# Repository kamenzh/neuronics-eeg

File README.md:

# Neuronic

An open development project for an affordable eight-channel EEG acquisition
PCB, ESP32 wireless streaming and PC-based signal processing and classification.

**Current revision A0.5** increases electrode series resistance, revises input filtering and rail discharge, updates the battery PTC and keys the controller harness. See the [protection review](docs/A0_5_PROTECTION.md) and [checked fabrication and hand-assembly files](hardware/fabrication/A0.5/). The Sino-k connector inquiry and assembled-system qualification are open.
There is no manufactured or body-validated Neuronic board yet. This repository
contains genuine KiCad source, not a manufacturing release.

**The target is a working eight-channel EEG instrument.** Bench testing is a
development phase; actual acquisition and person-use readiness still need
implementation, measurements and qualified system review. See the
[working-system acceptance plan](docs/SYSTEM_ACCEPTANCE_PLAN.md).

**November 19 follow-up:** the [independent November 17 report](docs/reviews/independent-577aad8-2026-11-17/REPORT.md)
is incorporated, the BOM prose is corrected, and a
[connector drawing/CAD audit](docs/CONNECTOR_VERIFICATION_A0_3.md) records what is
known and what still needs physical evidence. A0.5 fabrication data are available for review. Manufacturer selection and ordering are pending.

**A0.3 implements the main A0.2 review fixes:** revised analog routing,
stronger default logic pulls, two power-off tolerant interface buffers, extra
reference capacitance and revised socket mounting slots. Read the
[changes and remaining gates](docs/REVIEW_FIXES_A0_3.md). Historical
[A0.2 findings](docs/INDEPENDENT_REVIEW_A0_2.md) remain available.

**A0.5 controller cable.** Pin 1 is ground, position 2 is the mechanical key and must have no wire, pin 11 takes Nano 3V3, and pin 12 is GPIO6 enable. See the [cable pinout](docs/POWER_HARNESS_A0_3.md) and [keying instructions](docs/A0_5_PROTECTION.md).

**Controller selected: use the Waveshare ESP32-S3-Nano you already own.**
The Sino-k SGE117DN ten-lead set is recorded; P1 36619 touchproof sockets are selected; physical plug fit still needs verification. See [the wiring and power plan](docs/CONTROLLER_AND_ELECTRODES.md)
and [the step-by-step roadmap](docs/NEXT_STEPS.md).

**First time using KiCad? Read [START_HERE](docs/START_HERE.md).** Open
[`hardware/kicad/neuronic.kicad_pro`](hardware/kicad/neuronic.kicad_pro) in KiCad.

## System

```mermaid
flowchart TD
    E["8 contacts + reference"] --> P["Input networks"]
    P --> A["ADS1299: PGAs and simultaneous ADCs"]
    A -->|"3.3 V SPI"| M["External ESP32"]
    A --> B["Limited bias output: tenth contact"]
    M -->|"Wireless"| C["PC: recording and classification"]
    V["Battery and regulators"] --> A
```

| Parameter | A0.5 design target |
| --- | --- |
| Recording channels | 8 simultaneous |
| Contacts | 8 recording + 1 reference + 1 bias |
| Front end | ADS1299IPAG, programmable gain, 24-bit output |
| Initial rate | 250 samples/s/channel |
| Analog / ADC digital supplies | 5 V / 3.3 V |
| Input power | 6 x AA alkaline candidate; no charger |
| Controller interface | Waveshare ESP32-S3-Nano via 12-pin 3.3 V SPI header |
| PCB | 88 x 90 mm, four copper layers, routed bench prototype |

The ADS1299 already supplies the amplification and conversion. An additional
high-gain analog amplifier chain is not assumed. Nominal ADC bit depth is not
a claim of noise-free resolution, and more gain can reduce offset headroom.

## Repository map

| Path | Contents |
| --- | --- |
| `hardware/kicad/` | Main project, four schematic sheets, PCB, custom symbols and bundled footprints |
| `hardware/bom/` | Per-component and grouped candidate MPN lists; not an order release |
| `hardware/parts.json` | Editable candidate component catalog |
| `hardware/interface.json` | Selected controller GPIO, electrode and power contract |
| `hardware/design.json` | Generated component/net/placement record |
| `hardware/validation/` | Exported netlist, connectivity audit, DRC, RC calculation and sheet previews |
| `hardware/fabrication/` | A0.5 Gerber/drill package and assembly references for review |
| `firmware/` | Acquisition firmware specification; implementation pending |
| `software/` | PC receiver/recorder specification; implementation pending |
| `ml/` | Evaluation plan; no trained classifier yet |
| `experiments/` | Recording and validation protocols |
| `docs/` | Beginner guide, design decisions, open blockers and bench plan |
| `tools/` | Reproducible hardware generator and validation commands |
| `data/` | Local private recordings; contents ignored by Git |

The old CortexLink README is retained in `docs/archive/initial-README.md`.
The empty duplicate KiCad scaffolds were removed; their originals remain in
the repository history at `ae7d76e`.

## Verification

Read [the current status](hardware/validation/STATUS.md) before using the files.
Checks compare the **actual KiCad-exported netlist** with the source, component
footprints and an independent physical pin contract. They do not prove analog
performance, layout quality or body safety.

```bash
/usr/bin/python3 tools/validate_kicad.py
python3 tools/prepare_bom.py
python3 tools/review_electrical.py
python3 tools/check_contact_faults.py
python3 tools/simulate_input.py
/usr/bin/python3 -m unittest discover -s tests -v
```

Validation uses KiCad 9; on Linux use its compatible `/usr/bin/python3` for pcbnew. Read the current validation report for routing and CAD results; manufacturing and body-use approval remain separate. GUI ERC/DRC instructions are in the beginner guide.

See the [current protection review](docs/A0_5_PROTECTION.md) and [power and cable guide](docs/POWER_HARNESS_A0_3.md) for the circuit decisions and physical checks.

## Roadmap

- [x] Consolidate project and document circuit decisions.
- [x] Create editable KiCad sheets, footprint bundle, BOM and placed PCB.
- [x] Export and audit connectivity; perform limited ideal RC calculation.
- [ ] Close input-protection, connector, bias-loop and power-review blockers.
- [x] Complete a routed bench checkpoint with clean ERC and schematic-parity DRC.
- [x] Complete a separate AI review of the saved circuit and layout, with fresh checks and written findings.
- [x] Implement the main circuit/layout fixes and update checks/harness documentation.
- [ ] Verify physical fit and complete manufacturing-release review.
- [x] Select exact candidate PCB MPNs and the owned controller.
- [ ] Verify procurement details and compare delivered bare-board quotes.
- [ ] Fabricate a small prototype batch and complete bench tests.
- [ ] Implement and verify acquisition, raw recording and loss accounting.
- [ ] Review final body-connected design before scalp testing.
- [ ] Record repeatable EEG, then evaluate baselines and a CNN across sessions.

## Experiments and safety

The immediate target is trustworthy acquisition and a repeatable alpha
experiment. Intentional command classification follows measured signal quality.
EEG does not directly reveal arbitrary thoughts. Eye and muscle artifacts must
be checked, and train/test data must be separated by complete trials/sessions.

This is a body-connected engineering project, not a diagnostic device. A0.5 still needs
bench qualification and complete-system electrical safety review. Do not attach it to a person. Final electrode
protection and fault paths need qualified review before any scalp recording.
Battery power, ERC and DRC alone do not establish safety. During approved
recording, use a self-contained battery arrangement and wireless communication,
with USB, chargers and mains-connected instruments disconnected.

## Sources and licensing

See [design decisions and primary sources](docs/DESIGN_DECISIONS.md),
[open blockers](docs/REVIEW_BLOCKERS.md) and [third-party notices](hardware/licenses/).
The repository's existing MIT license is preserved for original work. Bundled
KiCad library assets retain their own license and design-use exception. No
third-party EEG hardware project has been silently relicensed or included.

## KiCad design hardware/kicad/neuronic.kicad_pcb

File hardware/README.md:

# Hardware

Open `kicad/neuronic.kicad_pro`. Read `validation/STATUS.md` and
`../docs/START_HERE.md` first.

`design.json` is generated by `tools/generate_hardware.py` and describes the
component/net/placement checkpoint. It is not a substitute for the actual
KiCad schematic or DRC. `bom/bom-review.csv` lists candidate parts and unresolved
MPNs; it is not a purchase-ready BOM.

KiCad source, script and review docs belong in Git. Fabrication files should
only be exported for reviewed, tagged hardware revisions.

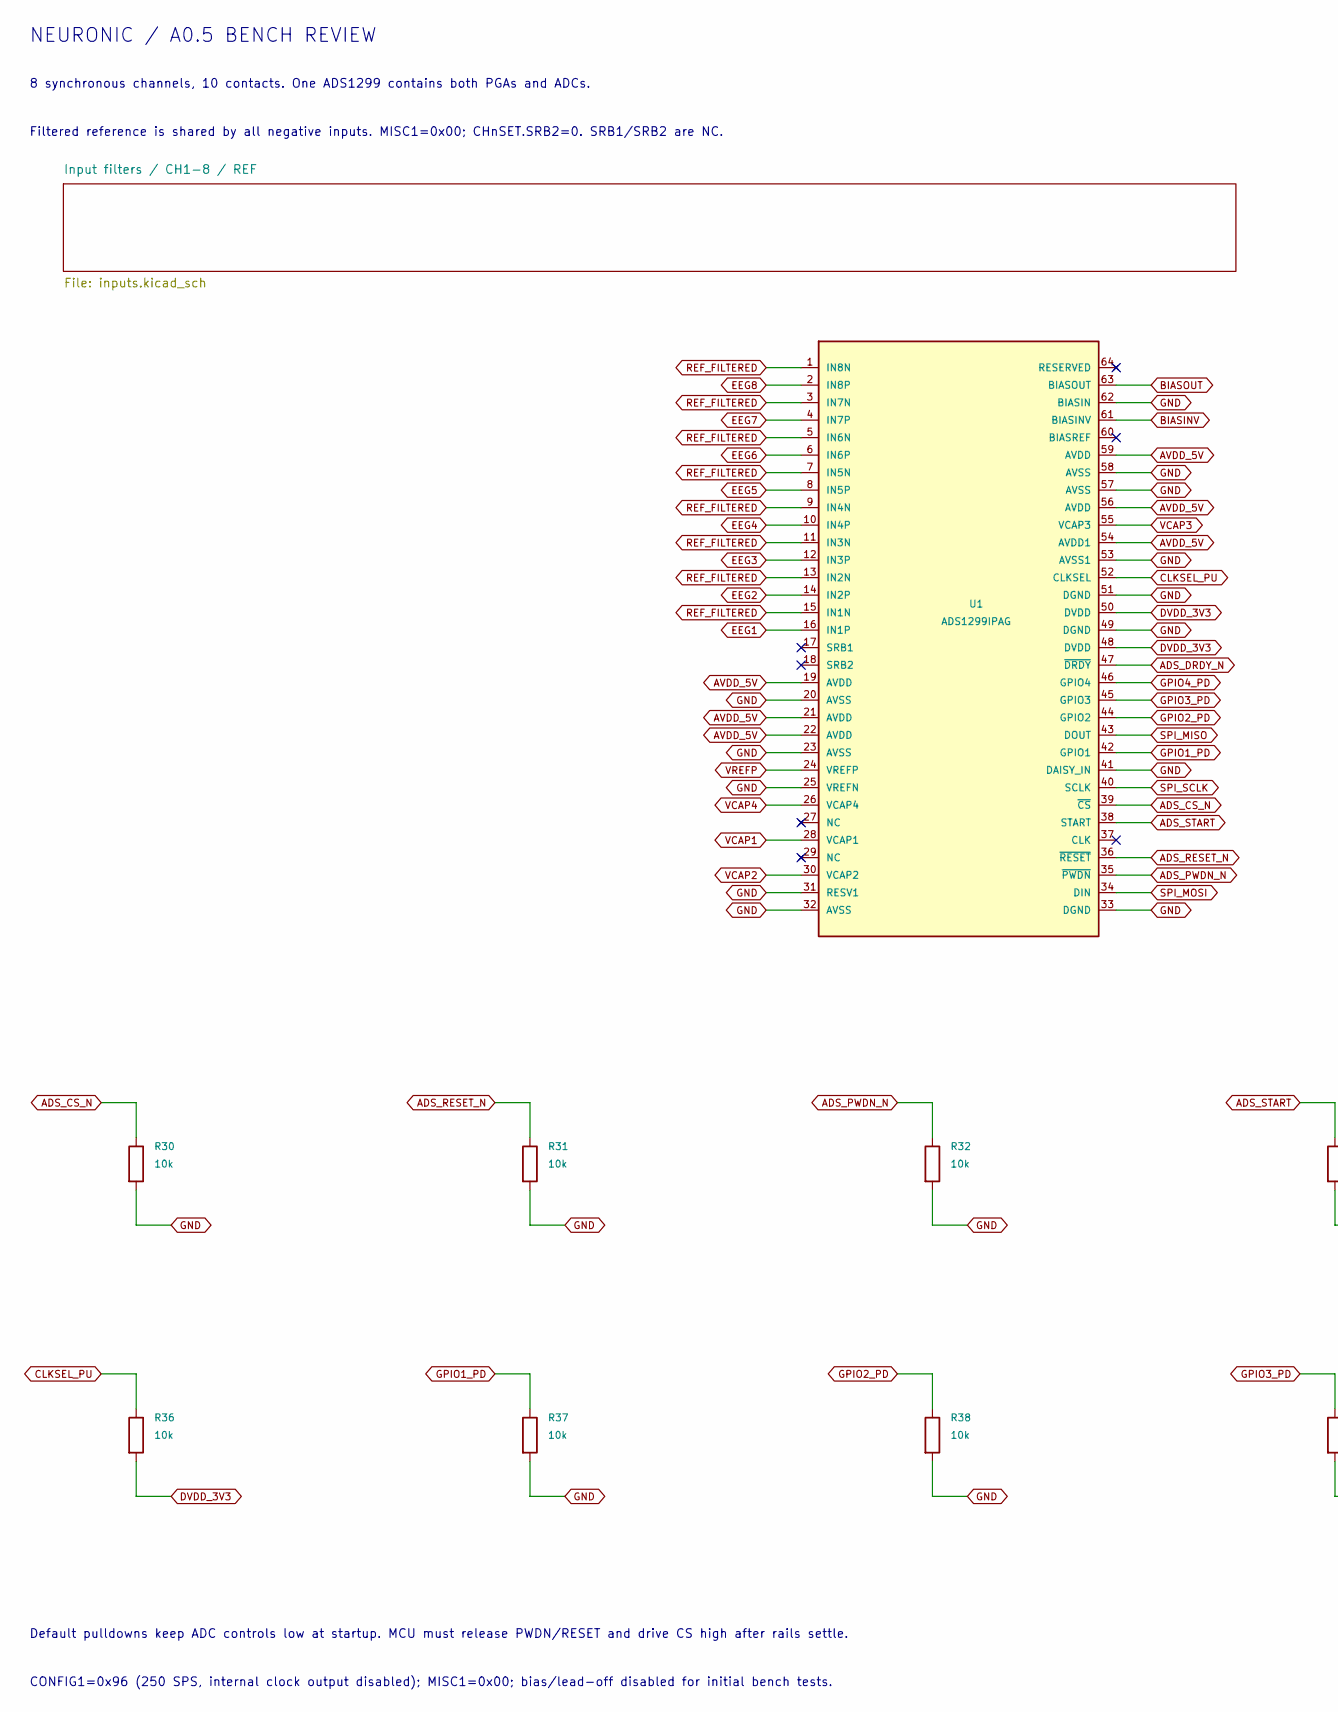
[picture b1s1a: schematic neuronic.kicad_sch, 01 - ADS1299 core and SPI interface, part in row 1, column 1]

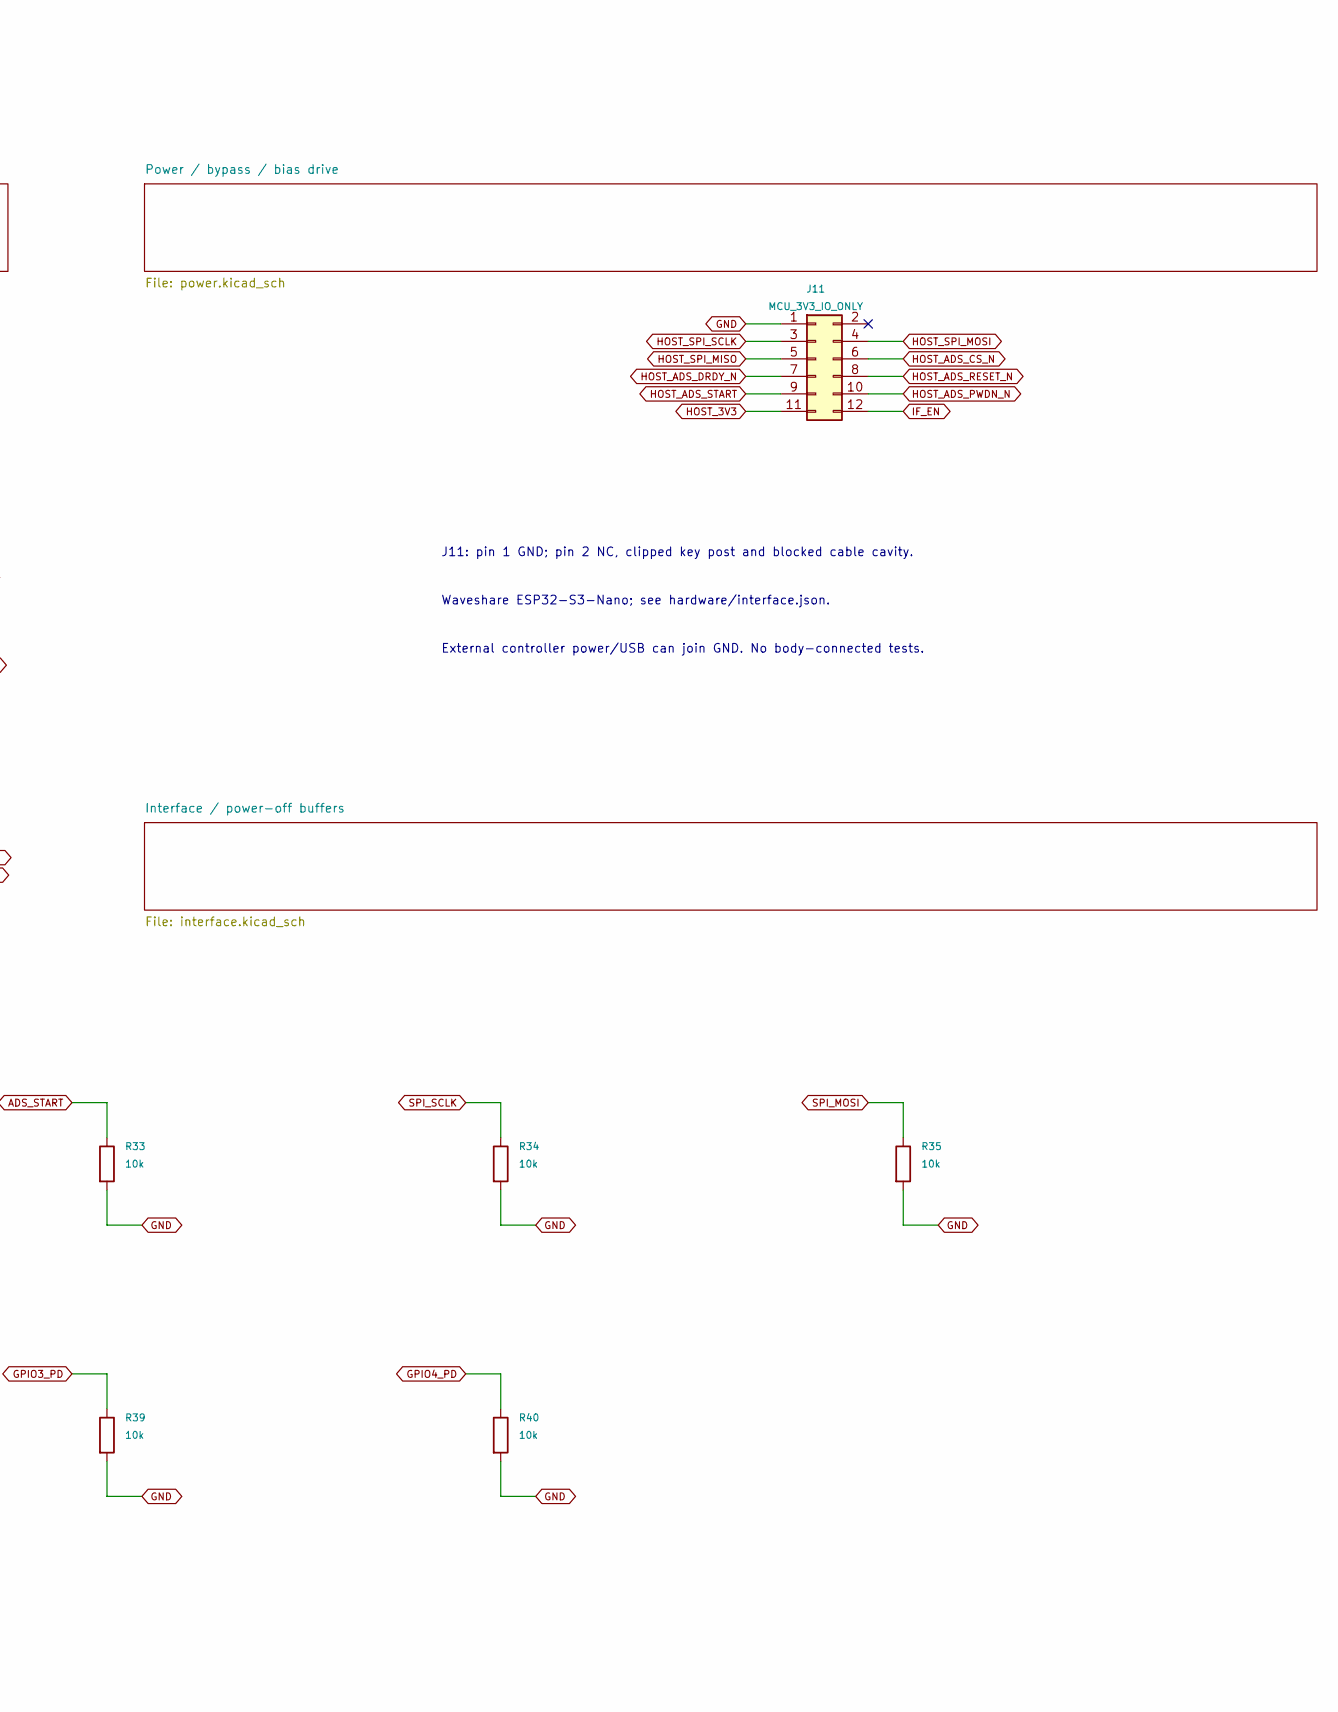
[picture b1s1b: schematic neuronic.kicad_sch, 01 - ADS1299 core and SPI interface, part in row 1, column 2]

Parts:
J11: MCU_3V3_IO_ONLY; PinHeader_2x06_P2.54mm_Vertical
R30, R31, R32, R33, R34, R35, R36, R37, R38, R39, R40: 10k; R_0805_2012Metric
U1: ADS1299IPAG; TQFP-64_10x10mm_P0.5mm

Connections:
ADS_CS_N: R30.1, U1.39 (~CS); also elsewhere on the board
ADS_DRDY_N: U1.47 (~DRDY); also elsewhere on the board
ADS_PWDN_N: R32.1, U1.35 (~PWDN); also elsewhere on the board
ADS_RESET_N: R31.1, U1.36 (~RESET); also elsewhere on the board
ADS_START: R33.1, U1.38 (START); also elsewhere on the board
AVDD_5V: U1.19 (AVDD), U1.21 (AVDD), U1.22 (AVDD), U1.54 (AVDD1), U1.56 (AVDD), U1.59 (AVDD); also elsewhere on the board
BIASINV: U1.61 (BIASINV); also elsewhere on the board
BIASOUT: U1.63 (BIASOUT); also elsewhere on the board
CLKSEL_PU: R36.1, U1.52 (CLKSEL)
DVDD_3V3: R36.2, U1.48 (DVDD), U1.50 (DVDD); also elsewhere on the board
EEG1: U1.16 (IN1P); also elsewhere on the board
EEG2: U1.14 (IN2P); also elsewhere on the board
EEG3: U1.12 (IN3P); also elsewhere on the board
EEG4: U1.10 (IN4P); also elsewhere on the board
EEG5: U1.8 (IN5P); also elsewhere on the board
EEG6: U1.6 (IN6P); also elsewhere on the board
EEG7: U1.4 (IN7P); also elsewhere on the board
EEG8: U1.2 (IN8P); also elsewhere on the board
GND: J11.1, R30.2, R31.2, R32.2, R33.2, R34.2, R35.2, R37.2, R38.2, R39.2, R40.2, U1.20 (AVSS), U1.23 (AVSS), U1.25 (VREFN), U1.31 (RESV1), U1.32 (AVSS), U1.33 (DGND), U1.41 (DAISY_IN), U1.49 (DGND), U1.51 (DGND), U1.53 (AVSS1), U1.57 (AVSS), U1.58 (AVSS), U1.62 (BIASIN); also elsewhere on the board
GPIO1_PD: R37.1, U1.42 (GPIO1)
GPIO2_PD: R38.1, U1.44 (GPIO2)
GPIO3_PD: R39.1, U1.45 (GPIO3)
GPIO4_PD: R40.1, U1.46 (GPIO4)
HOST_3V3: J11.11; also elsewhere on the board
HOST_ADS_CS_N: J11.6; also elsewhere on the board
HOST_ADS_DRDY_N: J11.7; also elsewhere on the board
HOST_ADS_PWDN_N: J11.10; also elsewhere on the board
HOST_ADS_RESET_N: J11.8; also elsewhere on the board
HOST_ADS_START: J11.9; also elsewhere on the board
HOST_SPI_MISO: J11.5; also elsewhere on the board
HOST_SPI_MOSI: J11.4; also elsewhere on the board
HOST_SPI_SCLK: J11.3; also elsewhere on the board
IF_EN: J11.12; also elsewhere on the board
REF_FILTERED: U1.1 (IN8N), U1.3 (IN7N), U1.5 (IN6N), U1.7 (IN5N), U1.9 (IN4N), U1.11 (IN3N), U1.13 (IN2N), U1.15 (IN1N); also elsewhere on the board
SPI_MISO: U1.43 (DOUT); also elsewhere on the board
SPI_MOSI: R35.1, U1.34 (DIN); also elsewhere on the board
SPI_SCLK: R34.1, U1.40 (SCLK); also elsewhere on the board
VCAP1: U1.28 (VCAP1); also elsewhere on the board
VCAP2: U1.30 (VCAP2); also elsewhere on the board
VCAP3: U1.55 (VCAP3); also elsewhere on the board
VCAP4: U1.26 (VCAP4); also elsewhere on the board
VREFP: U1.24 (VREFP); also elsewhere on the board

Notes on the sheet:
NEURONIC / A0.5 BENCH REVIEW
8 synchronous channels, 10 contacts. One ADS1299 contains both PGAs and ADCs.
Filtered reference is shared by all negative inputs. MISC1=0x00; CHnSET.SRB2=0. SRB1/SRB2 are NC.
J11: pin 1 GND; pin 2 NC, clipped key post and blocked cable cavity.
Waveshare ESP32-S3-Nano; see hardware/interface.json.
External controller power/USB can join GND. No body-connected tests.
Default pulldowns keep ADC controls low at startup. MCU must release PWDN/RESET and drive CS high after rails settle.
CONFIG1=0x96 (250 SPS, internal clock output disabled); MISC1=0x00; bias/lead-off disabled for initial bench tests.

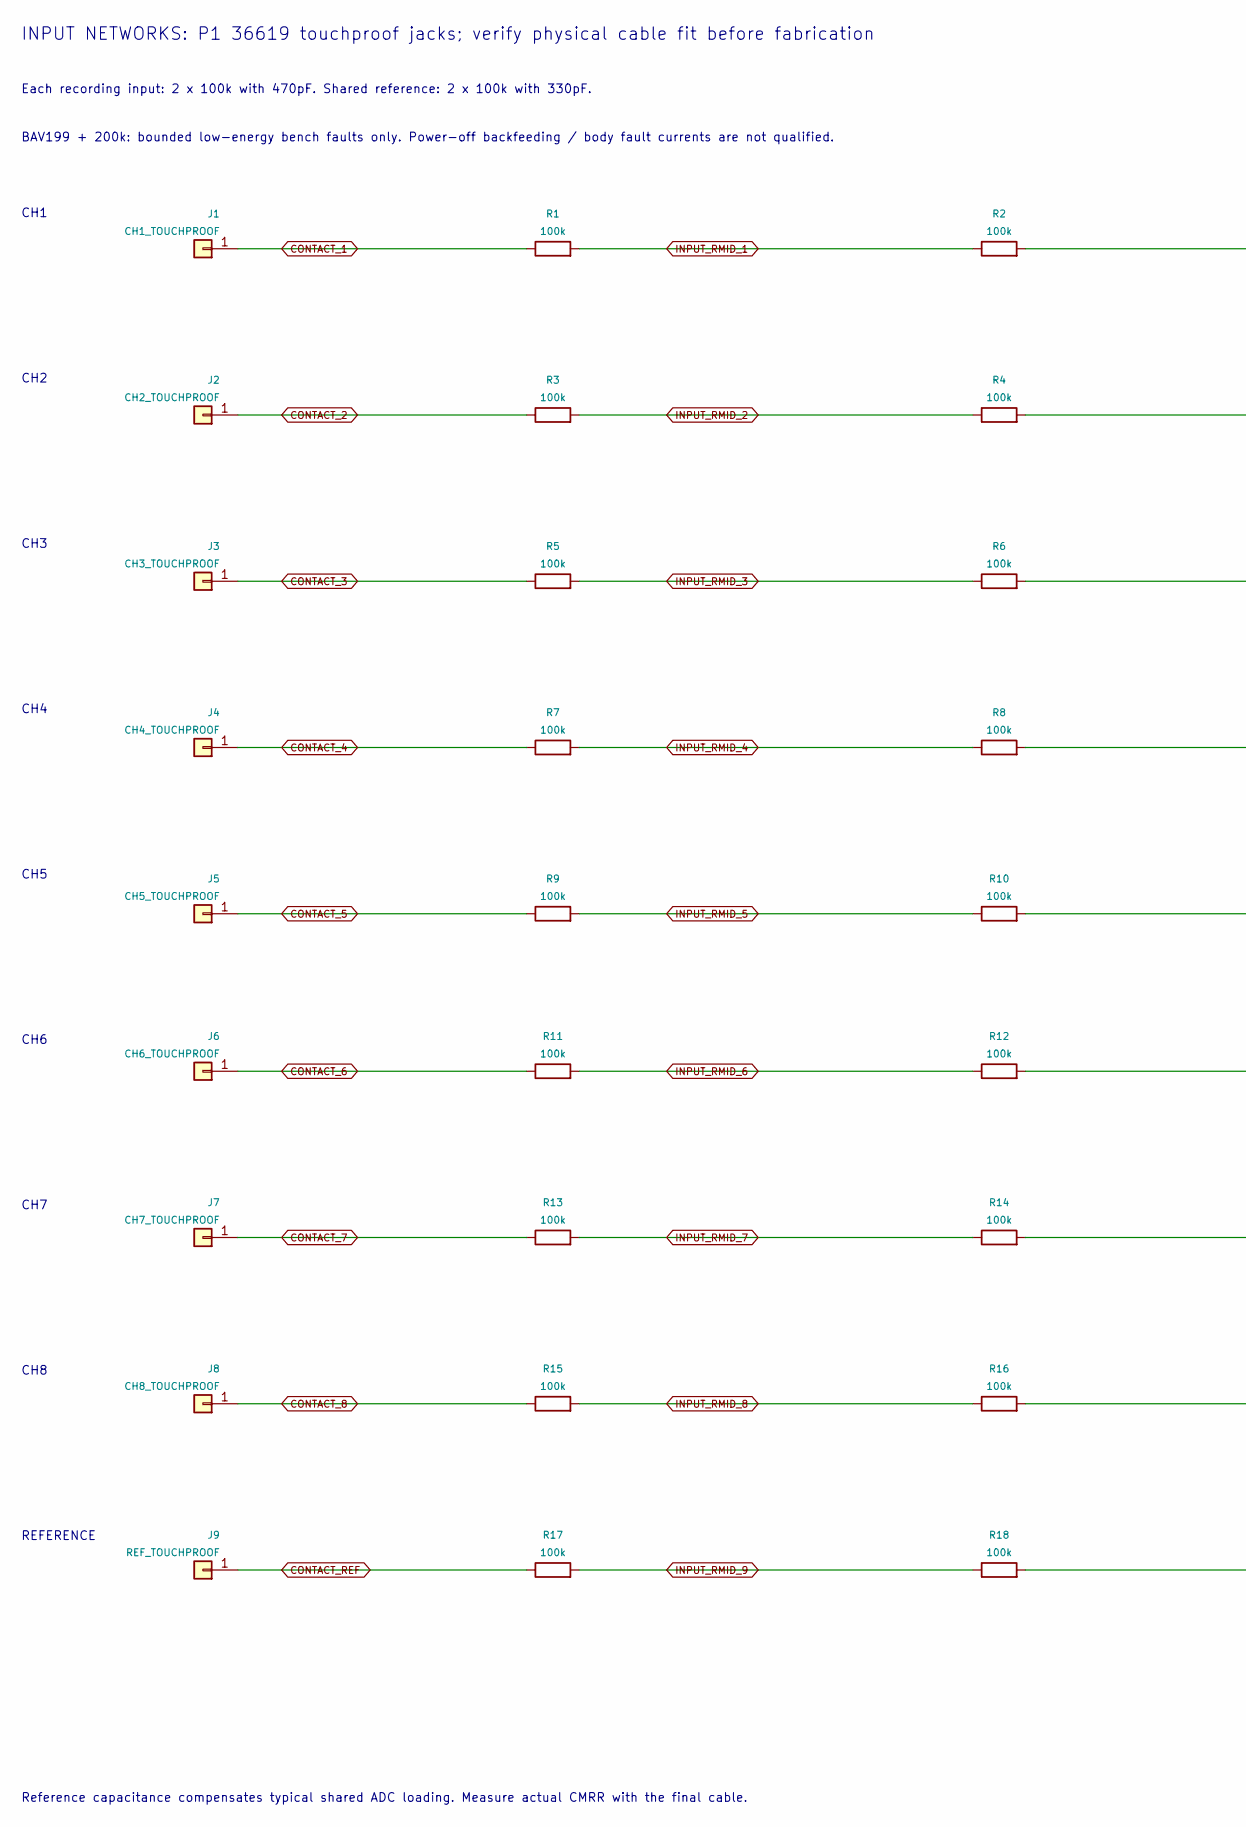
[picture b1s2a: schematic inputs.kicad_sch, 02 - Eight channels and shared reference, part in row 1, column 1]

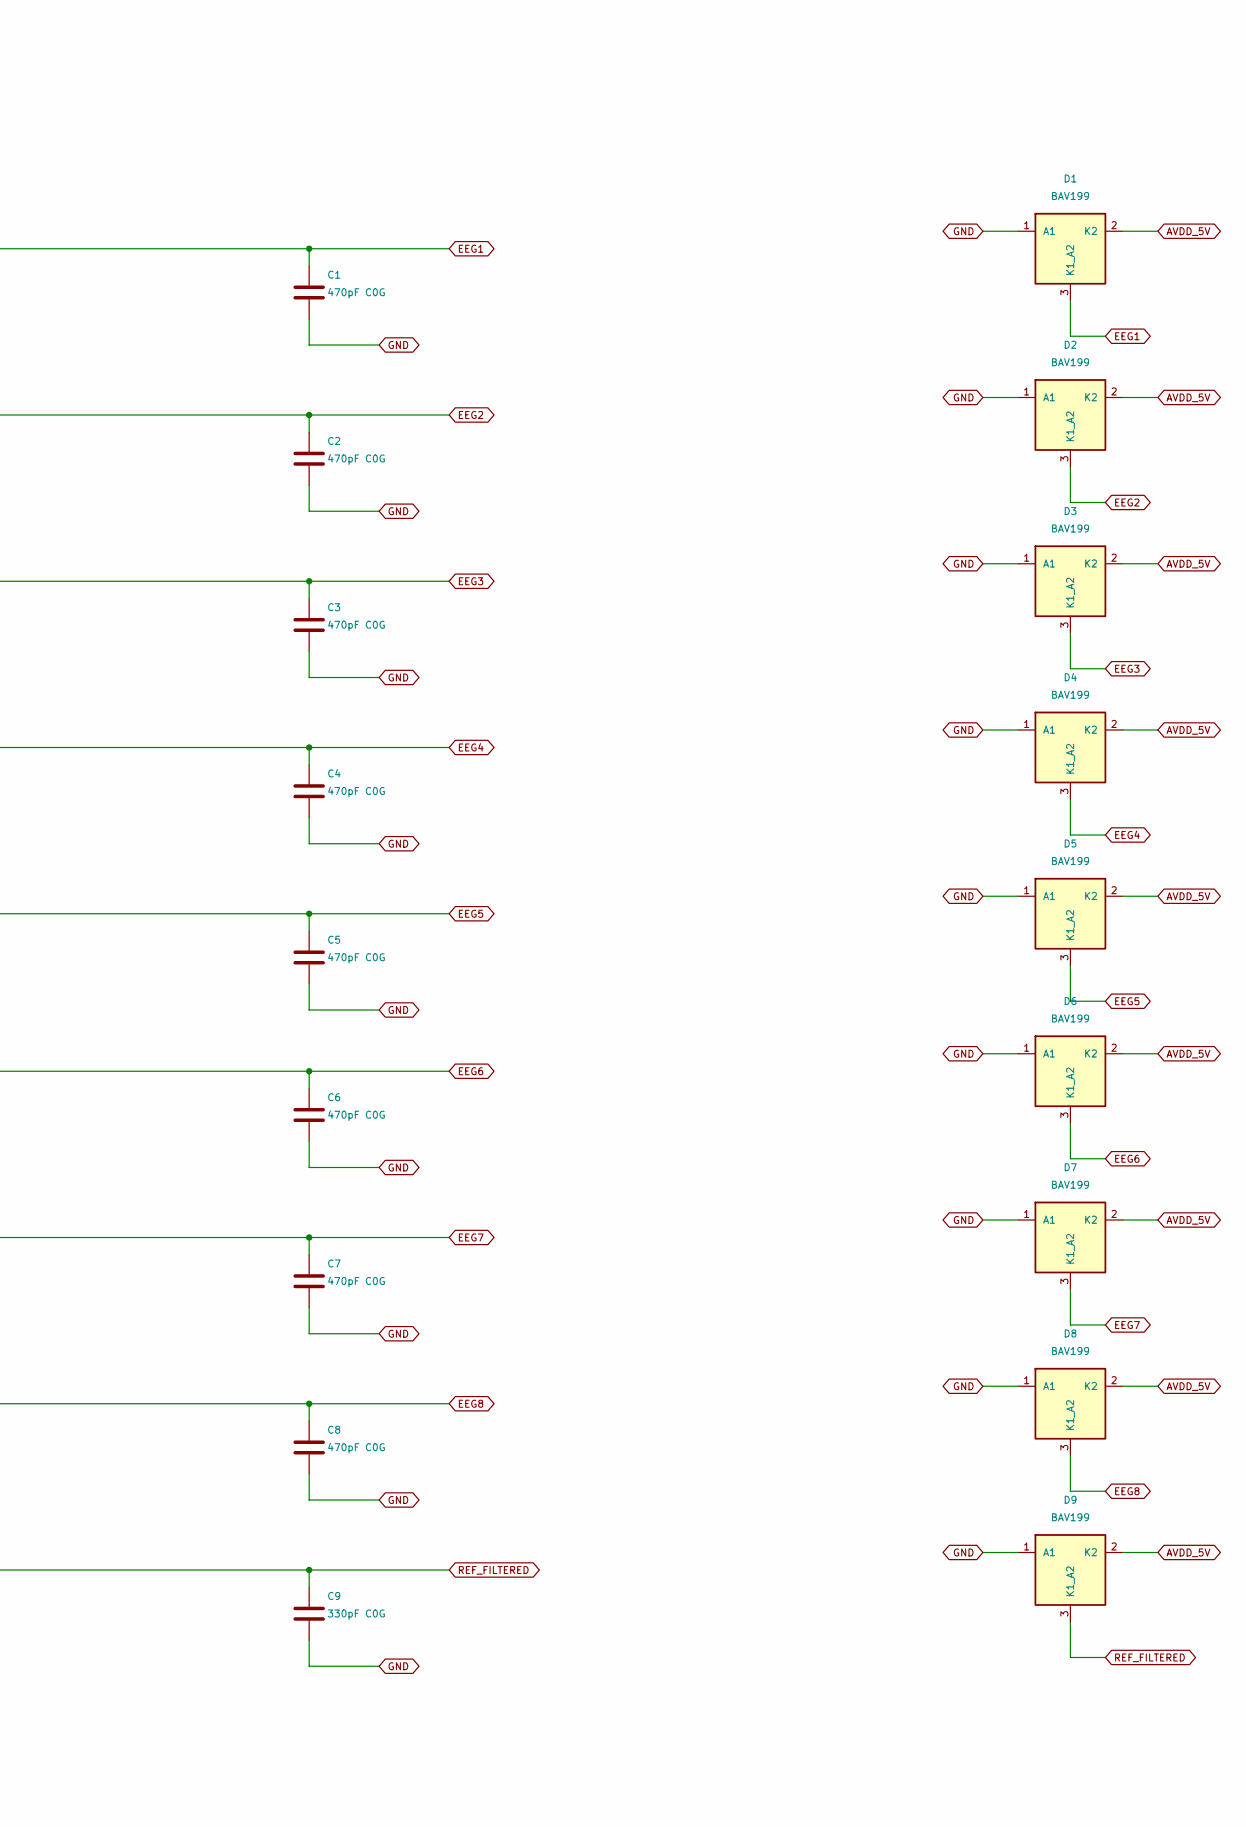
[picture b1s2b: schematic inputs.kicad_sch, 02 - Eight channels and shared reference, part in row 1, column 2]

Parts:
C1, C2, C3, C4, C5, C6, C7, C8: 470pF C0G; C_0805_2012Metric
C9: 330pF C0G; C_0805_2012Metric
D1, D2, D3, D4, D5, D6, D7, D8, D9: BAV199; SOT-23
J1: CH1_TOUCHPROOF; P1_36619_Touchproof_RA
J2: CH2_TOUCHPROOF; P1_36619_Touchproof_RA
J3: CH3_TOUCHPROOF; P1_36619_Touchproof_RA
J4: CH4_TOUCHPROOF; P1_36619_Touchproof_RA
J5: CH5_TOUCHPROOF; P1_36619_Touchproof_RA
J6: CH6_TOUCHPROOF; P1_36619_Touchproof_RA
J7: CH7_TOUCHPROOF; P1_36619_Touchproof_RA
J8: CH8_TOUCHPROOF; P1_36619_Touchproof_RA
J9: REF_TOUCHPROOF; P1_36619_Touchproof_RA
R1, R2, R3, R4, R5, R6, R7, R8, R9, R10, R11, R12, R13, R14, R15, R16, R17, R18: 100k; R_0805_2012Metric

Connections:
AVDD_5V: D1.2 (K2), D2.2 (K2), D3.2 (K2), D4.2 (K2), D5.2 (K2), D6.2 (K2), D7.2 (K2), D8.2 (K2), D9.2 (K2); also elsewhere on the board
CONTACT_1: J1.1, R1.1
CONTACT_2: J2.1, R3.1
CONTACT_3: J3.1, R5.1
CONTACT_4: J4.1, R7.1
CONTACT_5: J5.1, R9.1
CONTACT_6: J6.1, R11.1
CONTACT_7: J7.1, R13.1
CONTACT_8: J8.1, R15.1
CONTACT_REF: J9.1, R17.1
EEG1: C1.1, D1.3 (K1_A2), R2.2; also elsewhere on the board
EEG2: C2.1, D2.3 (K1_A2), R4.2; also elsewhere on the board
EEG3: C3.1, D3.3 (K1_A2), R6.2; also elsewhere on the board
EEG4: C4.1, D4.3 (K1_A2), R8.2; also elsewhere on the board
EEG5: C5.1, D5.3 (K1_A2), R10.2; also elsewhere on the board
EEG6: C6.1, D6.3 (K1_A2), R12.2; also elsewhere on the board
EEG7: C7.1, D7.3 (K1_A2), R14.2; also elsewhere on the board
EEG8: C8.1, D8.3 (K1_A2), R16.2; also elsewhere on the board
GND: C1.2, C2.2, C3.2, C4.2, C5.2, C6.2, C7.2, C8.2, C9.2, D1.1 (A1), D2.1 (A1), D3.1 (A1), D4.1 (A1), D5.1 (A1), D6.1 (A1), D7.1 (A1), D8.1 (A1), D9.1 (A1); also elsewhere on the board
INPUT_RMID_1: R1.2, R2.1
INPUT_RMID_2: R3.2, R4.1
INPUT_RMID_3: R5.2, R6.1
INPUT_RMID_4: R7.2, R8.1
INPUT_RMID_5: R9.2, R10.1
INPUT_RMID_6: R11.2, R12.1
INPUT_RMID_7: R13.2, R14.1
INPUT_RMID_8: R15.2, R16.1
INPUT_RMID_9: R17.2, R18.1
REF_FILTERED: C9.1, D9.3 (K1_A2), R18.2; also elsewhere on the board

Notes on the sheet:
INPUT NETWORKS: P1 36619 touchproof jacks; verify physical cable fit before fabrication
Each recording input: 2 x 100k with 470pF. Shared reference: 2 x 100k with 330pF.
BAV199 + 200k: bounded low-energy bench faults only. Power-off backfeeding / body fault currents are not qualified.
CH1
CH2
CH3
CH4
CH5
CH6
CH7
CH8
REFERENCE
Reference capacitance compensates typical shared ADC loading. Measure actual CMRR with the final cable.

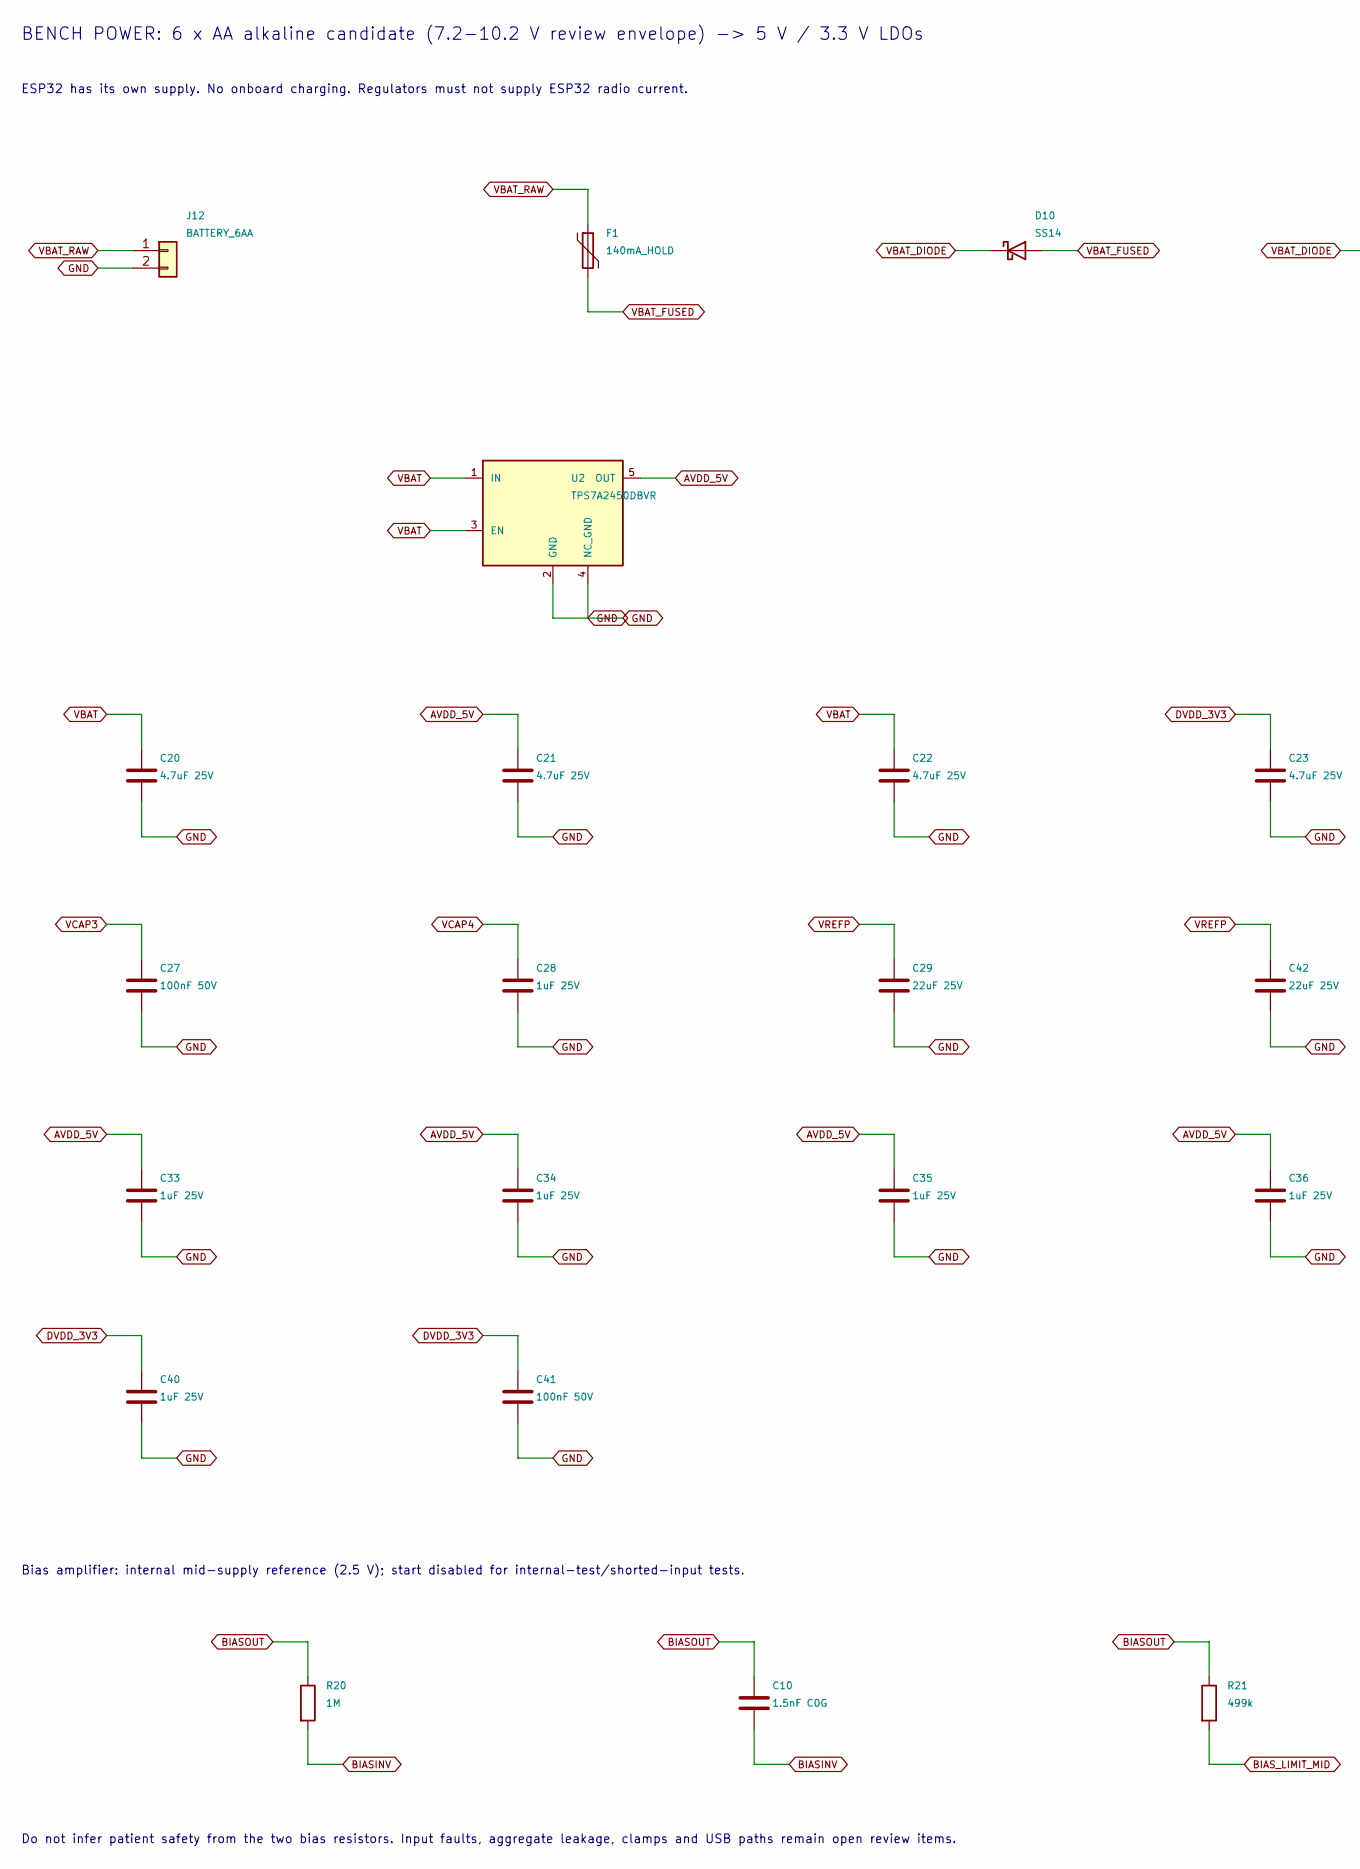
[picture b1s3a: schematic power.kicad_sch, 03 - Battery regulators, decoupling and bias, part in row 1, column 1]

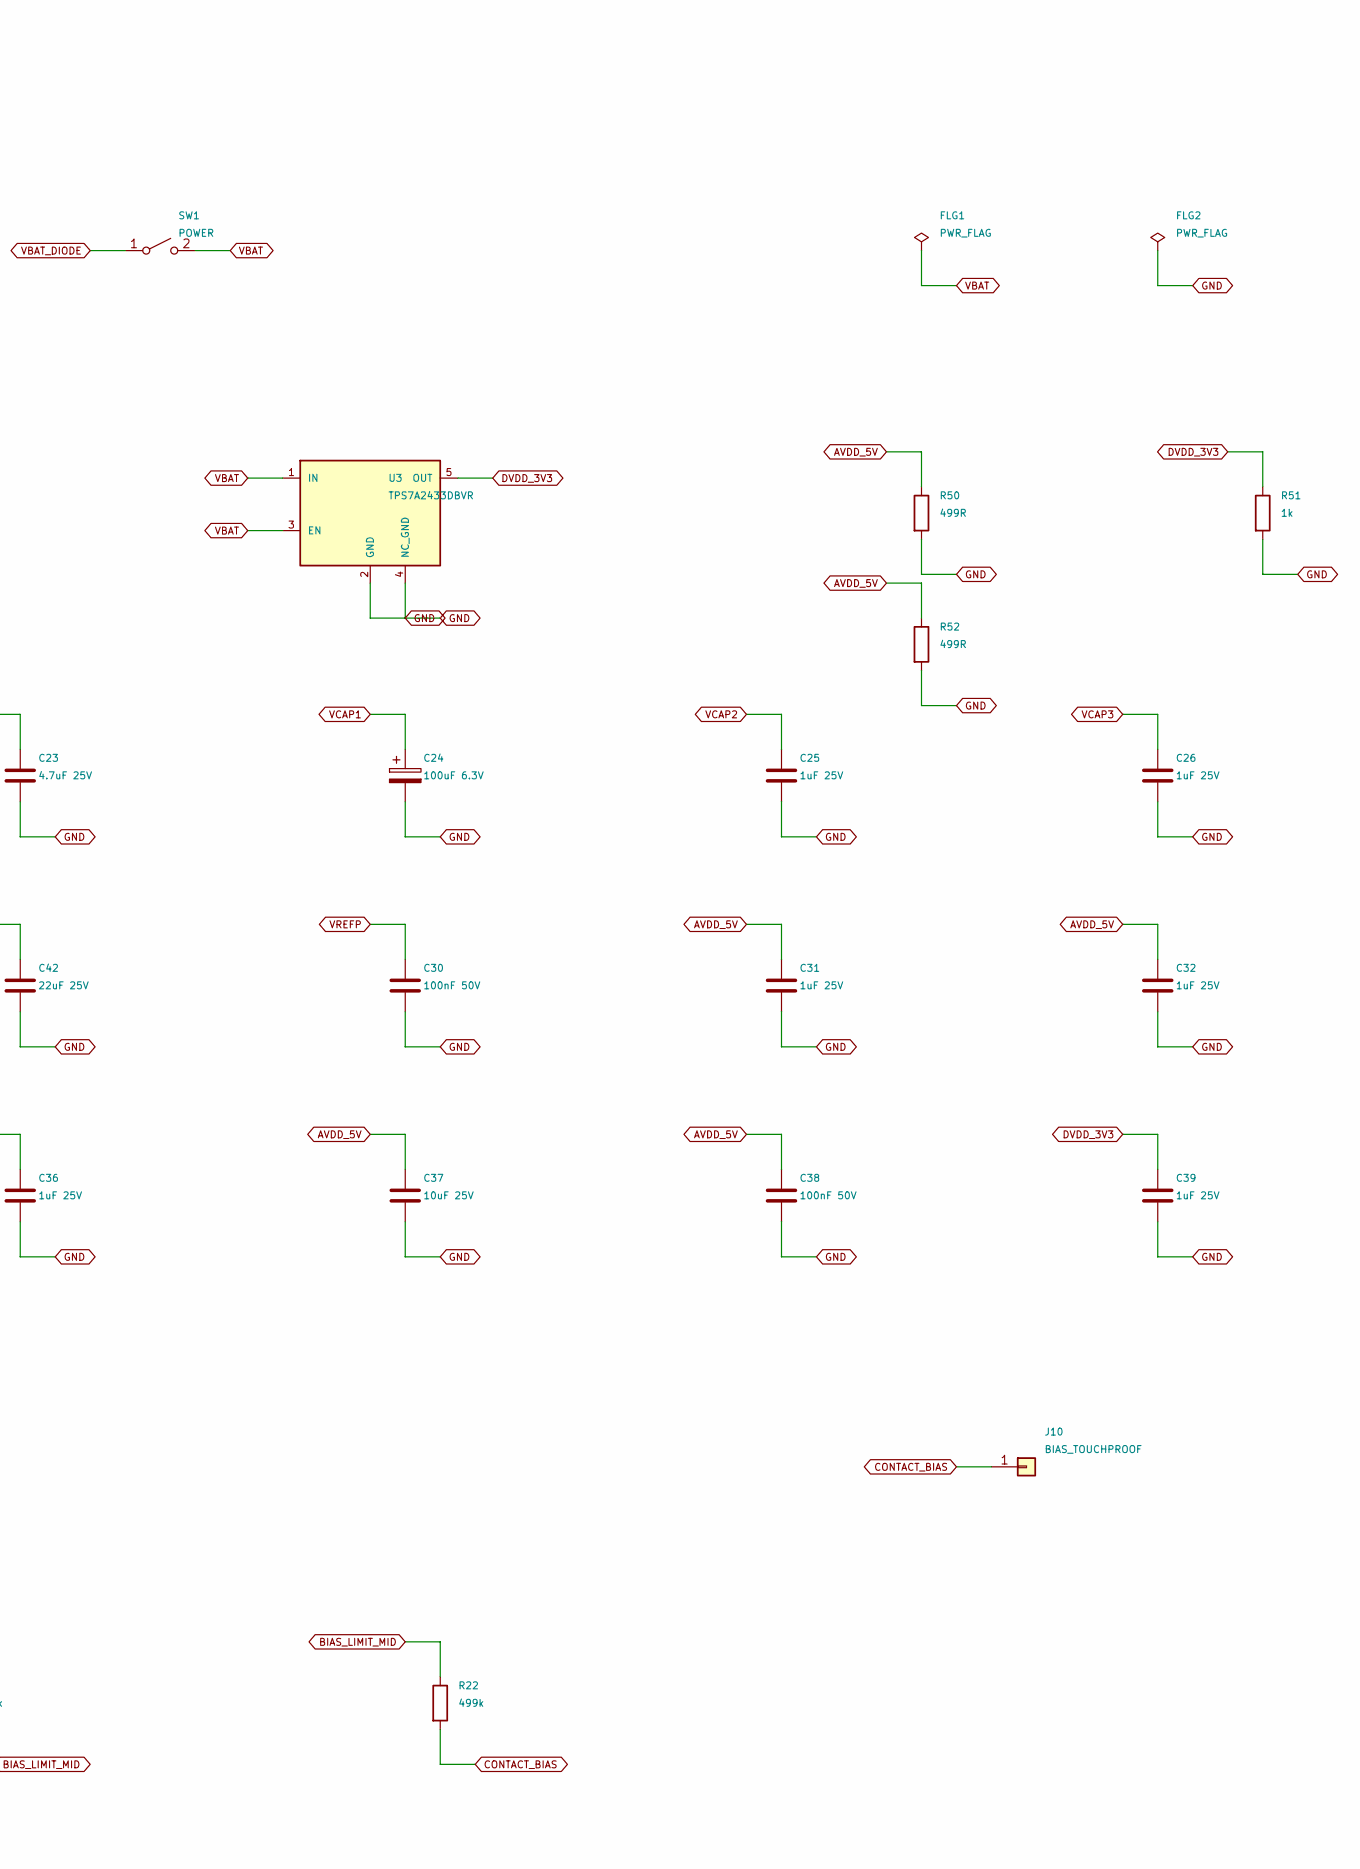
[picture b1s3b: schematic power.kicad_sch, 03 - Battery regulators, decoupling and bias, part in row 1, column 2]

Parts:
C10: 1.5nF C0G; C_0805_2012Metric
C20, C21, C22, C23: 4.7uF 25V; C_0805_2012Metric
C24: 100uF 6.3V; CP_EIA-3528-21_Kemet-B
C25, C26, C28, C31, C32, C33, C34, C35, C36, C39, C40: 1uF 25V; C_0805_2012Metric
C27, C30, C38, C41: 100nF 50V; C_0805_2012Metric
C29, C42: 22uF 25V; C_1210_3225Metric
C37: 10uF 25V; C_0805_2012Metric
D10: SS14; D_SMA
F1: 140mA_HOLD; Fuse_1812_4532Metric
FLG1, FLG2: PWR_FLAG
J10: BIAS_TOUCHPROOF; P1_36619_Touchproof_RA
J12: BATTERY_6AA; JST_XH_B2B-XH-A_1x02_P2.50mm_Vertical
R20: 1M; R_0805_2012Metric
R21, R22: 499k; R_0805_2012Metric
R50, R52: 499R; R_0805_2012Metric
R51: 1k; R_0805_2012Metric
SW1: POWER; PinHeader_1x02_P2.54mm_Vertical
U2: TPS7A2450DBVR; SOT-23-5
U3: TPS7A2433DBVR; SOT-23-5

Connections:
AVDD_5V: C21.1, C31.1, C32.1, C33.1, C34.1, C35.1, C36.1, C37.1, C38.1, R50.1, R52.1, U2.5 (OUT); also elsewhere on the board
BIASINV: C10.2, R20.2; also elsewhere on the board
BIASOUT: C10.1, R20.1, R21.1; also elsewhere on the board
BIAS_LIMIT_MID: R21.2, R22.1
CONTACT_BIAS: J10.1, R22.2
DVDD_3V3: C23.1, C39.1, C40.1, C41.1, R51.1, U3.5 (OUT); also elsewhere on the board
GND: C20.2, C21.2, C22.2, C23.2, C24.2, C25.2, C26.2, C27.2, C28.2, C29.2, C30.2, C31.2, C32.2, C33.2, C34.2, C35.2, C36.2, C37.2, C38.2, C39.2, C40.2, C41.2, C42.2, FLG2.1, J12.2, R50.2, R51.2, R52.2, U2.2 (GND), U2.4 (NC_GND), U3.2 (GND), U3.4 (NC_GND); also elsewhere on the board
VBAT: C20.1, C22.1, FLG1.1, SW1.2 (B), U2.1 (IN), U2.3 (EN), U3.1 (IN), U3.3 (EN)
VBAT_DIODE: D10.1 (K), SW1.1 (A)
VBAT_FUSED: D10.2 (A), F1.2
VBAT_RAW: F1.1, J12.1
VCAP1: C24.1; also elsewhere on the board
VCAP2: C25.1; also elsewhere on the board
VCAP3: C26.1, C27.1; also elsewhere on the board
VCAP4: C28.1; also elsewhere on the board
VREFP: C29.1, C30.1, C42.1; also elsewhere on the board

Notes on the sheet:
BENCH POWER: 6 x AA alkaline candidate (7.2-10.2 V review envelope) -> 5 V / 3.3 V LDOs
ESP32 has its own supply. No onboard charging. Regulators must not supply ESP32 radio current.
Bias amplifier: internal mid-supply reference (2.5 V); start disabled for internal-test/shorted-input tests.
Do not infer patient safety from the two bias resistors. Input faults, aggregate leakage, clamps and USB paths remain open review items.
